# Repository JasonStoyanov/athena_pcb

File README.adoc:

= Athena Project PCB
:hardbreaks-option:

Additional information regarding the hardware can be found in the following article:
https://open4tech.com/how-to-create-a-ble-sensor-beacon-part-1-the-hardware/

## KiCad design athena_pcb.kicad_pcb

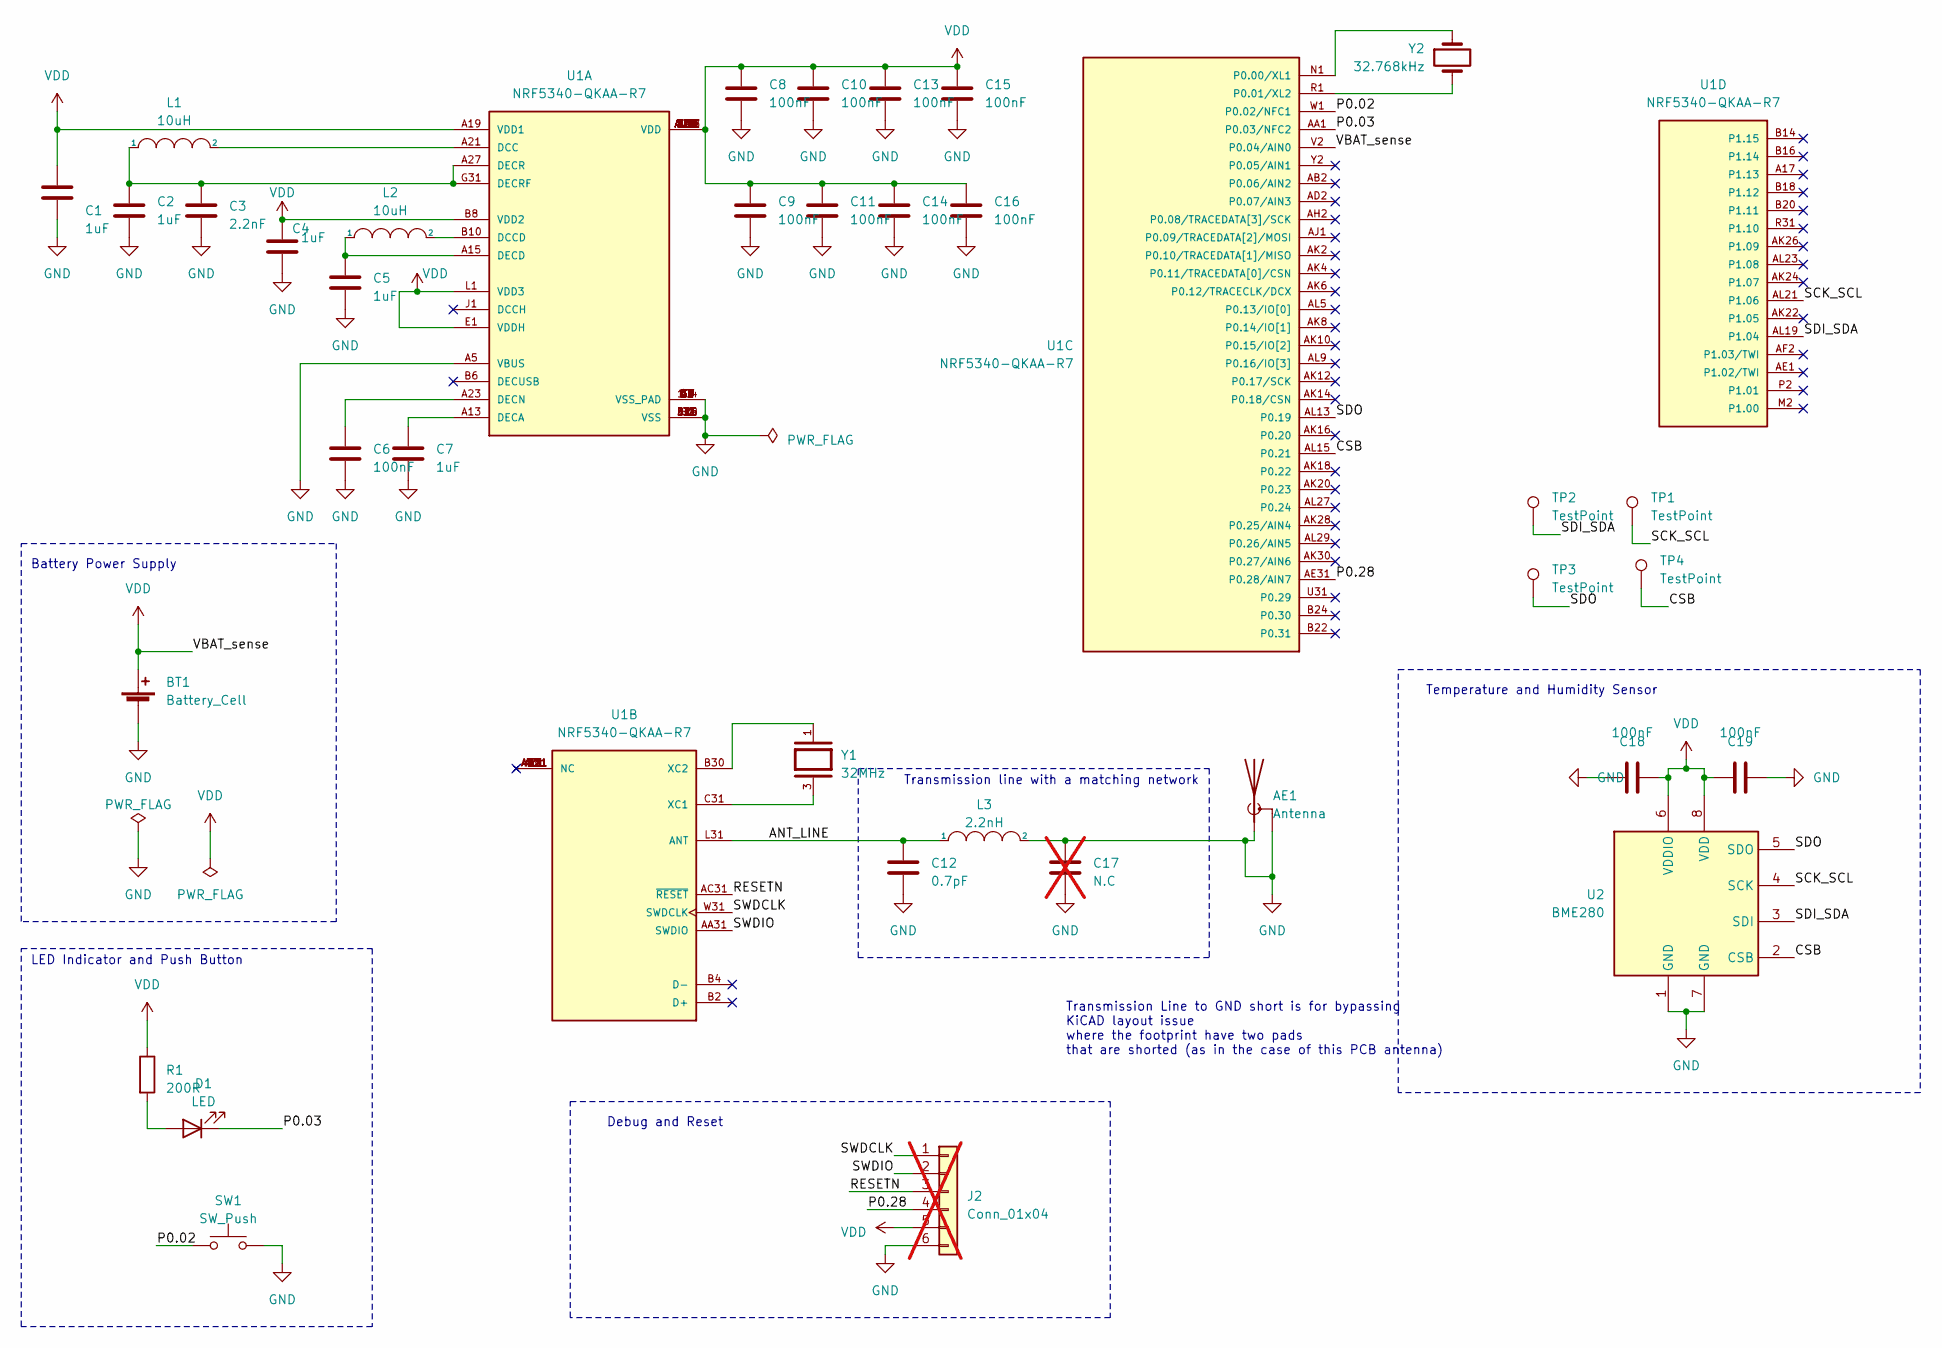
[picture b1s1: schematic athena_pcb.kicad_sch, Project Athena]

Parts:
AE1: Antenna; Texas_SWRA117D_2.4GHz_Right; MPN N.A
BT1: Battery_Cell; BatteryHolder_Keystone_1060_1x2032; MPN 1060
C1, C2, C4, C5, C7: 1uF; C_0402_1005Metric; MPN GRM155R61E105KA12D
C3: 2.2nF; CAPC0603X33N; MPN GRM033R61A222KA01D
C6, C8, C9, C10, C11, C13, C14, C15, C16, C18, C19: 100nF; CAPC0603X33N; MPN GRM033R60J104KE19D
C12: 0.7pF; CAPC0603X33N; MPN GJM0335C1HR70WB01D
C17: N.C; CAPC0603X33N; MPN N.A; not fitted
D1: LED; LED_0603_1608Metric; MPN 150060VS55040
J2: Conn_01x04; PinSocket_1x06_P1.27mm_Vertical; MPN N.A; not fitted
L1, L2: 10uH; INDC1608X95N; MPN LQM18DN100M70L
L3: 2.2nH; IND_LQP03HQ2N2B02D; MPN LQP03HQ2N2B02D
R1: 200R; R_0402_1005Metric; MPN RC0402FR-13200RL
SW1: SW_Push; SW_Push_1P1T_NO_CK_KMR2; MPN KMR221NGLFS
TP1, TP2, TP3, TP4: TestPoint; TestPoint_Pad_D1.0mm; MPN N.A
U1: NRF5340-QKAA-R7; XCVR_NRF5340-QKAA-R7; PARTREV 1.0
U2: BME280; Bosch_LGA-8_2.5x2.5mm_P0.65mm_ClockwisePinNumbering; MPN BME280
Y1: 32MHz; OSC_XRCGB32M000F1H19R0; PARTREV N/A
Y2: 32.768kHz; XTAL_CM8V-T1A-32.768KHZ-9PF-20PPM-TA-QC; MPN CM8V-T1A-32.768kHz-9pF-20PPM-TA-QC

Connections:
/ANT_LINE: C12.1, L3.1, U1.L31 (ANT)
/CSB: TP4.1, U1.AL15 (P0.21), U2.2 (CSB)
/P0.02: SW1.1, U1.W1 (P0.02/NFC1)
/P0.03: D1.1 (K), U1.AA1 (P0.03/NFC2)
/P0.28: J2.4, U1.AE31 (P0.28/AIN7)
/RESETN: J2.3, U1.AC31 (~RESET)
/SCK_SCL: TP1.1, U1.AL21 (P1.06), U2.4 (SCK)
/SDI_SDA: TP2.1, U1.AL19 (P1.04), U2.3 (SDI)
/SDO: TP3.1, U1.AL13 (P0.19), U2.5 (SDO)
/SWDCLK: J2.1, U1.W31 (SWDCLK)
/SWDIO: J2.2, U1.AA31 (SWDIO)
GND: AE1.1 (A), AE1.2 (Shield), BT1.2 (-), C1.2, C2.2, C3.2, C4.2, C5.2, C6.2, C7.2, C8.2, C9.2, C10.2, C11.2, C12.2, C13.2, C14.2, C15.2, C16.2, C17.1, C17.2, C18.1, C19.2, J2.6, L3.2, SW1.2, U1.35 (VSS_PAD), U1.36 (VSS_PAD), U1.37 (VSS_PAD), U1.38 (VSS_PAD), U1.39 (VSS_PAD), U1.40 (VSS_PAD), U1.41 (VSS_PAD), U1.43 (VSS_PAD), U1.44 (VSS_PAD), U1.45 (VSS_PAD), U1.46 (VSS_PAD), U1.47 (VSS_PAD), U1.48 (VSS_PAD), U1.49 (VSS_PAD), U1.50 (VSS_PAD), U1.51 (VSS_PAD), U1.104 (VSS_PAD), U1.A5 (VBUS), U1.A25 (VSS), U1.B12 (VSS), U1.B26 (VSS), U1.G1 (VSS), U1.H2 (VSS), U1.J31 (VSS), U2.1 (GND), U2.7 (GND)
unnamed: D1.2 (A), R1.2
unnamed: L1.2, U1.A21 (DCC)
unnamed: L2.2, U1.B10 (DCCD)
unnamed: C7.1, U1.A13 (DECA)
unnamed: C5.1, L2.1, U1.A15 (DECD)
unnamed: C6.1, U1.A23 (DECN)
unnamed: C2.1, C3.1, L1.1, U1.A27 (DECR), U1.G31 (DECRF)
unnamed: U1.C31 (XC1), Y1.3
unnamed: U1.B30 (XC2), Y1.1
unnamed: U1.N1 (P0.00/XL1), Y2.1
unnamed: U1.R1 (P0.01/XL2), Y2.2
VDD: BT1.1 (+), C1.1, C4.1, C8.1, C9.1, C10.1, C11.1, C13.1, C14.1, C15.1, C16.1, C18.2, C19.1, J2.5, R1.1, U1.A19 (VDD1), U1.AC1 (VDD), U1.AG1 (VDD), U1.AJ31 (VDD), U1.AL3 (VDD), U1.AL7 (VDD), U1.AL11 (VDD), U1.AL17 (VDD), U1.AL25 (VDD), U1.B8 (VDD2), U1.B28 (VDD), U1.C1 (VDD), U1.E1 (VDDH), U1.E31 (VDD), U1.L1 (VDD3), U1.N31 (VDD), U1.U1 (VDD), U1.V2 (P0.04/AIN0), U2.6 (VDDIO), U2.8 (VDD)

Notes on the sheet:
Battery Power Supply
Debug and Reset
Transmission line with a matching network
Temperature and Humidity Sensor
LED Indicator and Push Button
Transmission Line to GND short is for bypassing KiCAD layout issue where the footprint have two pads that are shorted (as in the case of this PCB antenna)

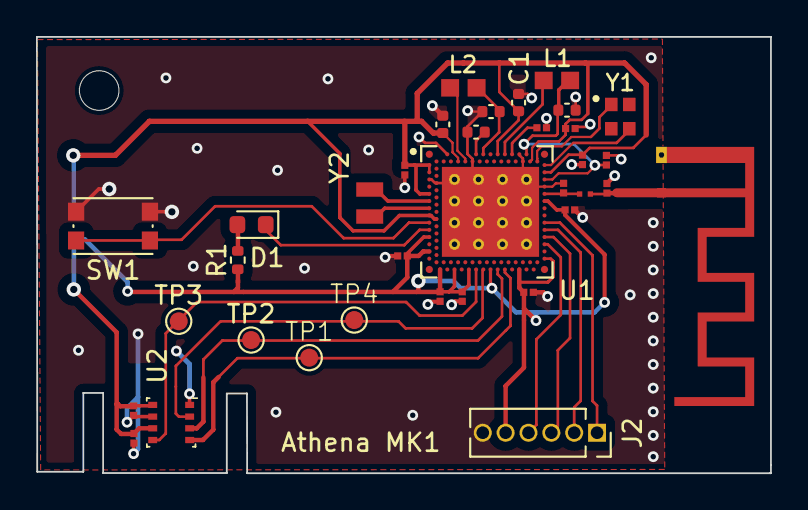
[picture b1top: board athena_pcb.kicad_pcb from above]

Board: 2 copper layers, 40.8 x 24.2 mm, 36 parts (1 on the bottom side), 24 nets.

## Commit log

2023-02-06 Power and Ground connection as per reference schematic
2023-02-07 Additional connections made
2023-02-11 BME280 shcematic done
2023-02-13 Updated to KiCAD 7. Added VBAT Sense
2023-02-14 Added user button and indicator LED
2023-02-18 Added footprint to capacitors
2023-02-18 Added footprint and symbol for the NRF53
2023-02-20 Added board layout constraints
2023-02-23 Layout around NRF53 done
2023-03-07 Added new 0201 capacitor footprint
2023-03-15 Added board outline
2023-03-20 Added testpoints
2023-03-22 Added Vias acc. to PCB fab
2023-03-24 Adapted PCB antenna footprint to use polygon, Workaroung for schematic symbol
2023-03-25 Added proper Y1 symbol and footprint
2023-03-27 Polishing layout
2023-03-28 Updated Header pinout, added ground pours to PCB
2023-03-31 Changes from the review
2023-04-03 Added items in the BOM
2023-04-06 Bom updated, not connected added to nrf53 pins
2023-04-08 Cleaned Track not connected Warnings
2023-04-08 Updated tracks to 6mils where possible
2023-04-10 Added edge clearence, transmission line width to match with pcb antenna feed
2023-04-21 Version sent to PCB manufacturer
2024-09-08 ADOC Readme added
